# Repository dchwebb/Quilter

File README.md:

# Quilter

Quilter
--------

Quilter is a four-voice polyphonic analog low pass filter designed for use with the Eurorack Modular Synthesiser architecture.

As part of a range of compatilble Mountjoy Modular modules, polyphonic interconnections are made using RJ-45 cables (as used for Ethernet).

Each of the four filters is a four-pole self-oscillating low pass filter. Cutoff is controlled by a combination of shared signals (frequency potentiometer and jack socket) and two individual  controls frequency controls (one at approximately half the sensitivity of the other) available on RJ-45 connectors.

Resonance is controlled from a potentiometer with self-oscillation available at extreme settings.

Polyphonic output is available from an RJ-45 socket and a mixed output is available on a 3.5mm jack socket.

The module is built around the Sound Semiconductor SSI2144 Fatkeys Four-Pole Voltage Controlled Filter. A number of TL074/TL072 op-amps are used for control signal mixing, buffering and output amplification.

Two trimmer potentiometers are available for each voice to control volt per octave when using the filter in self-resonant mode, and frequency offset to control the base frequency of the cut-off of each voice.

Technical
---------

Construction is a sandwich of three PCBs with a component board, a controls board and a panel. PCBs designed in Kicad v6.

[Components schematic](https://raw.githubusercontent.com/dchwebb/Quilter/master/Quilter_Components.pdf)

[Controls schematic](https://raw.githubusercontent.com/dchwebb/Quilter/master/Quilter_Controls.pdf)

### Power

The Eurorack +/-12V rails have reverse polarity protection and filtering.

- +12V Current Draw: 52mA
- -12V Current Draw: 50mA

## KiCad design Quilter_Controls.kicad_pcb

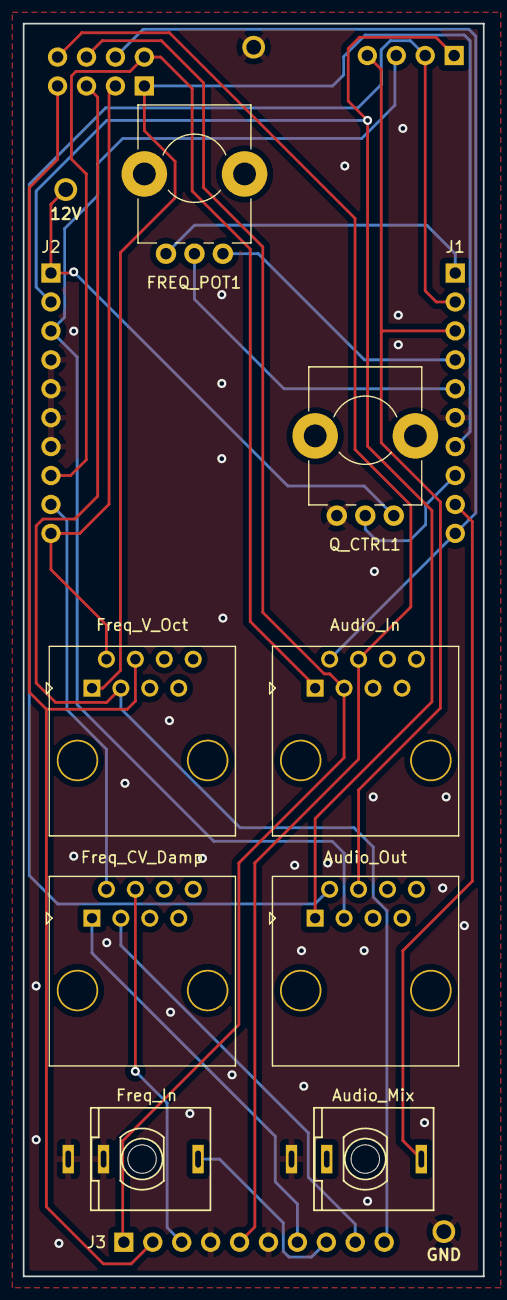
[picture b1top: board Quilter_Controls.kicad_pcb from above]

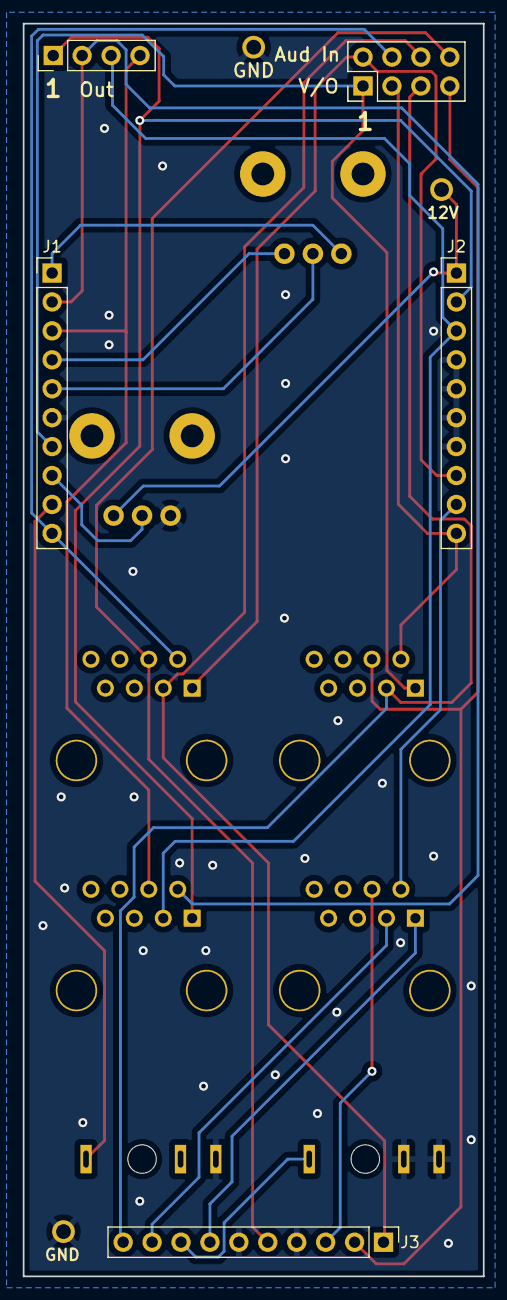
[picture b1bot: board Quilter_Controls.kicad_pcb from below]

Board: 2 copper layers, 40.4 x 110.0 mm, 16 parts (5 on the bottom side), 24 nets.

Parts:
FREQ_POT1: 10k; Alpha_9mm_Potentiometer_Aligned
J1, J2, J3: Conn_01x10_Male; PinHeader_1x10_P2.54mm_Vertical
J4: Audio_In; RJ45_Molex_42878-8506
J5: Audio_Out; RJ45_Molex_42878-8506
J6: Audio_Mix; THONKICONN_hole
J7: Freq_V_Oct; RJ45_Molex_42878-8506
J8: Freq_CV_Damp; RJ45_Molex_42878-8506
J9: Conn_02x04_Top_Bottom; PinHeader_2x04_P2.54mm_Vertical
J10: Conn_01x04_Male; PinHeader_1x04_P2.54mm_Vertical
J11: Freq_In; THONKICONN_hole
Q_CTRL1: 10k; Alpha_9mm_Potentiometer_Aligned
TP1, TP3, TP4: TestPoint; 1.3mm_Test_Point

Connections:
+12V: J2.1, Q_CTRL1.1, TP1.1
/AUDIO_BUFF1: J2.2, J5.1, J10.1
/AUDIO_BUFF2: J1.2, J5.2, J10.2
/AUDIO_BUFF3: J2.3, J5.3, J10.3
/AUDIO_BUFF4: J1.3, J5.4, J10.4
/AUDIO_IN1: J2.8, J4.1, J9.2
/AUDIO_IN2: J1.10, J4.2, J9.4
/AUDIO_IN3: J3.1, J4.3, J9.6
/AUDIO_IN4: J3.5, J4.4, J9.8
/AUDIO_MIX: J1.9, J6.3
/FREQ_CV_DAMP1: J3.7, J8.1
/FREQ_CV_DAMP2: J2.9, J8.2
/FREQ_CV_DAMP3: J3.9, J8.3
/FREQ_CV_DAMP4: J3.3, J8.4
/FREQ_JACK: J3.8, J11.3
/FREQ_POT: FREQ_POT1.2, J1.5
/FREQ_POT_5V: FREQ_POT1.1, J1.4
/FREQ_POT_-5V: FREQ_POT1.3, J1.1
/FREQ_V_OCT1: J1.7, J7.1, J9.1
/FREQ_V_OCT2: J2.10, J7.2, J9.3
/FREQ_V_OCT3: J3.10, J7.3, J9.5
/FREQ_V_OCT4: J3.2, J7.4, J9.7
/Q_POT: J1.8, Q_CTRL1.2
GND: J1.6, J2.4, J2.5, J2.6, J2.7, J3.4, J3.6, J6.1, J11.1, J11.2, Q_CTRL1.3, TP3.1, TP4.1

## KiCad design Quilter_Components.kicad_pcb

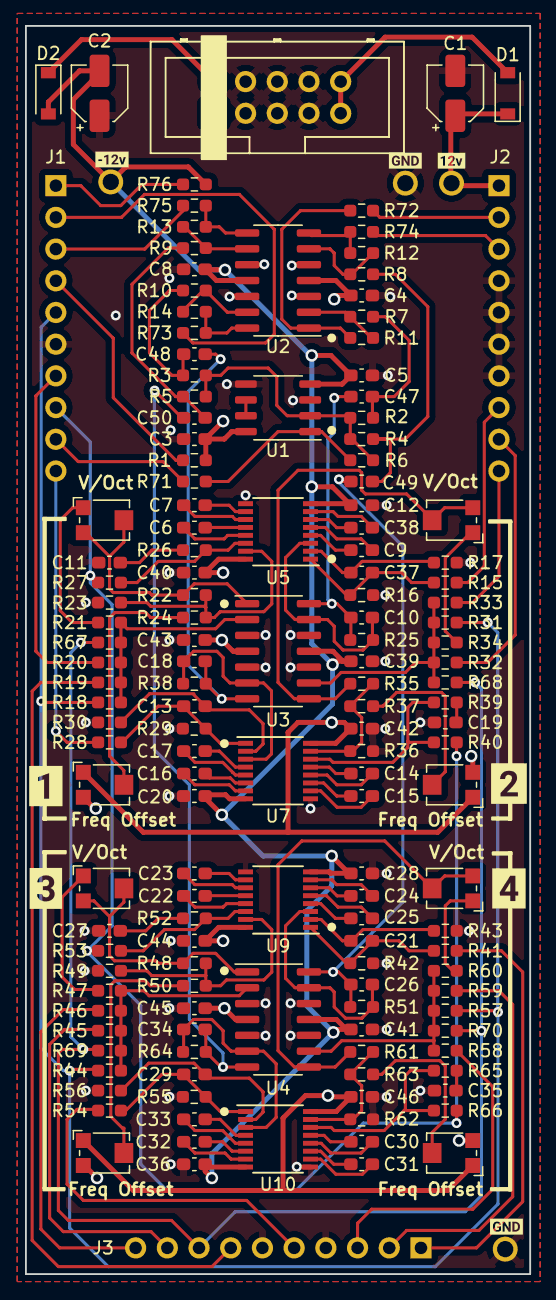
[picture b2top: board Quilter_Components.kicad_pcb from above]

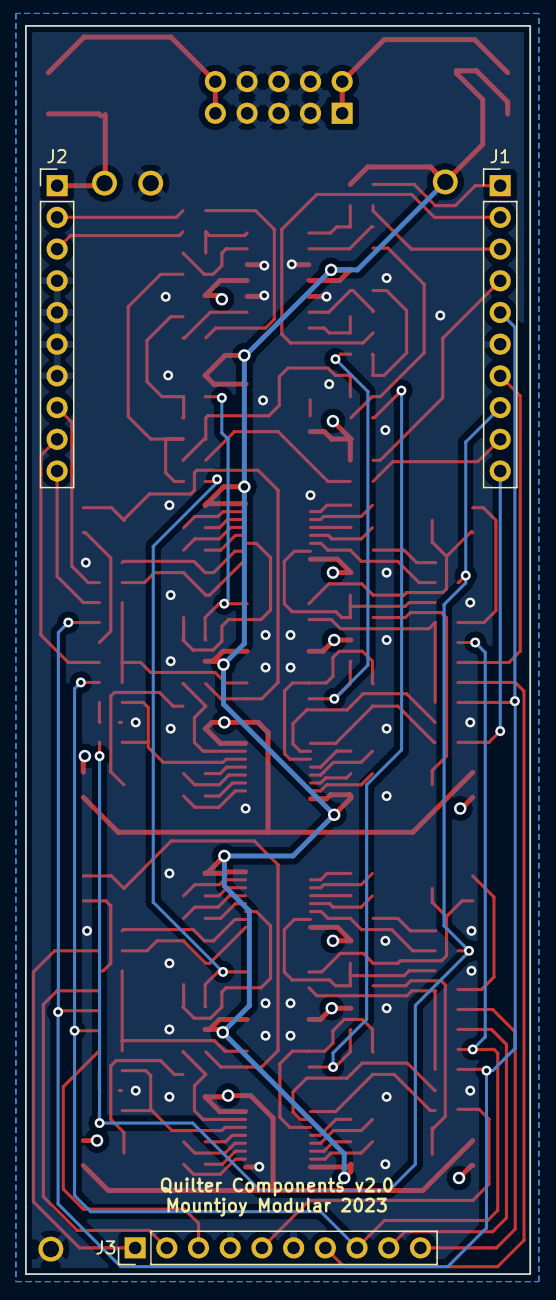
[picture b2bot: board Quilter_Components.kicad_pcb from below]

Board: 4 copper layers, 40.4 x 100.0 mm, 160 parts (3 on the bottom side), 118 nets.

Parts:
C1, C2: 22uF; CP_Elec_4x5.8
C3, C4, C5, C8, C12, C20, C28, C36, C39, C40, C41, C42, C43, C44, C45, C46: 1uF; C_0603_1608Metric_Pad1.08x0.95mm_HandSolder
C6, C7, C14, C15, C16, C22, C23, C24, C30, C31, C32, C38: 6.8nF_C0G; C_0603_1608Metric_Pad1.08x0.95mm_HandSolder
C9, C17, C25, C33: 560pF_C0G; C_0603_1608Metric_Pad1.08x0.95mm_HandSolder
C10, C18, C26, C34: 100pF; C_0603_1608Metric_Pad1.08x0.95mm_HandSolder
C11, C19, C27, C35: 10nF; C_0603_1608Metric_Pad1.08x0.95mm_HandSolder
C13, C21, C29, C37: 3.3nF; C_0603_1608Metric_Pad1.08x0.95mm_HandSolder
C47, C48, C49, C50: 10uF; C_0603_1608Metric_Pad1.08x0.95mm_HandSolder
D1, D2: 1N5819; D_SOD-123
FREQ_OFFSET1, FREQ_OFFSET2, FREQ_OFFSET3, FREQ_OFFSET4: 50k; Potentiometer_Bourns_TC33X_Vertical
J1, J2, J3: Conn_01x10_Male; PinHeader_1x10_P2.54mm_Vertical
J4: Eurorack_10_pin_power; Eurorack_10_pin_header
R1, R76: 14k; R_0603_1608Metric_Pad0.98x0.95mm_HandSolder
R2, R3, R4, R5, R7, R8, R9, R10, R11, R12, R13, R14: 10k; R_0603_1608Metric_Pad0.98x0.95mm_HandSolder
R6: 4.7k; R_0603_1608Metric_Pad0.98x0.95mm_HandSolder
R15, R28, R41, R54: 68k; R_0603_1608Metric_Pad0.98x0.95mm_HandSolder
R16, R17, R29, R30, R42, R43, R55, R56: 200; R_0603_1608Metric_Pad0.98x0.95mm_HandSolder
R18, R20, R22, R31, R33, R35, R44, R46, R48, R57, R59, R61, R67, R68, R69, R70: 100k; R_0603_1608Metric_Pad0.98x0.95mm_HandSolder
R19, R32, R45, R58: 220k; R_0603_1608Metric_Pad0.98x0.95mm_HandSolder
R21, R34, R47, R60: 160k; R_0603_1608Metric_Pad0.98x0.95mm_HandSolder
R23, R36, R49, R62, R71, R72, R73, R74, R75: 1k; R_0603_1608Metric_Pad0.98x0.95mm_HandSolder
R24, R37, R50, R63: 499k; R_0603_1608Metric_Pad0.98x0.95mm_HandSolder
R25, R38, R51, R64: 33k; R_0603_1608Metric_Pad0.98x0.95mm_HandSolder
R26, R39, R52, R65: 499; R_0603_1608Metric_Pad0.98x0.95mm_HandSolder
R27, R40, R53, R66: 24k; R_0603_1608Metric_Pad0.98x0.95mm_HandSolder
TP1, TP2, TP3, TP4: TestPoint; 1.3mm_Test_Point
U1: TL072; SO-8_3.9x4.9mm_P1.27mm
U2, U3, U4: TL074; SOIC-14_3.9x8.7mm_P1.27mm
U5, U7, U9, U10: SSI2144; SSOP-16_3.9x4.9mm_P0.635mm
V_OCT1, V_OCT2, V_OCT3, V_OCT4: 50k; Potentiometer_Bourns_TC33X_Vertical
kibuzzard-63F9EC4B: G***; kibuzzard-63F9EC4B
kibuzzard-63F9ECEE: G***; kibuzzard-63F9ECEE
kibuzzard-63FCE890: G***; kibuzzard-63FCE890
kibuzzard-63FCEF0D: G***; kibuzzard-63FCEF0D
kibuzzard-640237A8: G***; kibuzzard-640237A8
kibuzzard-640237DF, kibuzzard-640237DF#2: G***; kibuzzard-640237DF
kibuzzard-640237FD: G***; kibuzzard-640237FD

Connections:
+12V: C1.1, C3.1, C4.1, C40.1, C42.1, C43.1, C44.1, C45.1, C46.1, D1.1 (K), FREQ_OFFSET1.1, FREQ_OFFSET2.1, FREQ_OFFSET3.1, FREQ_OFFSET4.1, J2.1, R1.1, TP1.1, U1.8 (V+), U2.4 (V+), U3.4 (V+), U4.4 (V+), U5.16 (V+), U7.16 (V+), U9.16 (V+), U10.16 (V+)
-12V: C2.2, C5.1, C8.1, C12.2, C20.2, C28.2, C36.2, C39.1, C41.1, D2.2 (A), FREQ_OFFSET1.3, FREQ_OFFSET2.3, FREQ_OFFSET3.3, FREQ_OFFSET4.3, R76.1, TP2.1, U1.4 (V-), U2.11 (V-), U3.11 (V-), U4.11 (V-), U5.8 (V-), U7.8 (V-), U9.8 (V-), U10.8 (V-)
/+12V_IN: D1.2 (A), J4.9, J4.10
/-12V_IN: D2.1 (K), J4.1, J4.2
/AUDIO_BUFF1: J2.2, R72.2
/AUDIO_BUFF2: J1.2, R73.2
/AUDIO_BUFF3: J2.3, R74.2
/AUDIO_BUFF4: J1.3, R75.2
/AUDIO_IN1: J2.8, R15.2
/AUDIO_IN2: J1.10, R28.2
/AUDIO_IN3: J3.1, R41.2
/AUDIO_IN4: J3.5, R54.2
/AUDIO_MIX: J1.9, R71.2
/Audio_Out1: C47.1, R2.2, R7.2
/Audio_Out2: C48.1, R3.2, R10.2
/Audio_Out3: C49.1, R4.2, R8.2
/Audio_Out4: C50.1, R5.2, R9.2
/FREQ_CV_DAMP1: J3.7, R19.2
/FREQ_CV_DAMP2: J2.9, R32.2
/FREQ_CV_DAMP3: J3.9, R45.2
/FREQ_CV_DAMP4: J3.3, R58.2
/FREQ_JACK: J3.8, R67.2, R68.2, R69.2, R70.2
/FREQ_POT: J1.5, R18.2, R31.2, R44.2, R57.2
/FREQ_POT_5V: J1.4, R1.2
/FREQ_POT_-5V: J1.1, R76.2
/FREQ_V_OCT1: J1.7, R20.2
/FREQ_V_OCT2: J2.10, R33.2
/FREQ_V_OCT3: J3.10, R46.2
/FREQ_V_OCT4: J3.2, R59.2
/Filter_Voice1/FREQ_CTRL: R22.1, R23.1, R24.1, U5.15 (FREQ_CTRL)
/Filter_Voice1/Q_CTRL: R26.2, R27.2, U5.14 (Q_CTRL)
/Filter_Voice2/FREQ_CTRL: R35.1, R36.1, R37.1, U7.15 (FREQ_CTRL)
/Filter_Voice2/Q_CTRL: R39.2, R40.2, U7.14 (Q_CTRL)
/Filter_Voice3/FREQ_CTRL: R48.1, R49.1, R50.1, U9.15 (FREQ_CTRL)
/Filter_Voice3/Q_CTRL: R52.2, R53.2, U9.14 (Q_CTRL)
/Filter_Voice4/FREQ_CTRL: R61.1, R62.1, R63.1, U10.15 (FREQ_CTRL)
/Filter_Voice4/Q_CTRL: R65.2, R66.2, U10.14 (Q_CTRL)
/Q_POT: J1.8, R27.1, R40.1, R53.1, R66.1
GND: C1.2, C2.1, C3.2, C4.2, C5.2, C8.2, C11.2, C12.1, C19.2, C20.1, C27.2, C28.1, C35.2, C36.1, C39.2, C40.2, C41.2, C42.2, C43.2, C44.2, C45.2, C46.2, J1.6, J2.4, J2.5, J2.6, J2.7, J3.4, J3.6, J4.3, J4.4, J4.5, J4.6, J4.7, J4.8, R16.1, R17.2, R23.2, R29.1, R30.2, R36.2, R42.1, R43.2, R49.2, R55.1, R56.2, R62.2, TP3.1, TP4.1, U1.3 (+), U1.5 (+), U2.3 (+), U2.5 (+), U2.10 (+), U2.12 (+), U3.3 (+), U3.5 (+), U3.10 (+), U3.12 (+), U4.3 (+), U4.5 (+), U4.10 (+), U4.12 (+), U5.9 (GND), U7.9 (GND), U9.9 (GND), U10.9 (GND)
unnamed: C6.1, U5.13 (C1A)
unnamed: C6.2, U5.12 (C1B)
unnamed: C7.1, U5.11 (C2A)
unnamed: C7.2, U5.10 (C2B)
unnamed: C9.1, U5.4 (C4A)
unnamed: C9.2, U5.5 (C4B)
unnamed: C10.1, C47.2, R25.1, U3.14
unnamed: C10.2, R25.2, U3.13 (-), U5.3 (OUT)
unnamed: C11.1, R26.1
unnamed: C13.1, R30.1, U7.2 (SIG_IN-)
unnamed: C13.2, R28.1, R29.2, U7.1 (SIG_IN+)
unnamed: C14.1, U7.13 (C1A)
unnamed: C14.2, U7.12 (C1B)
unnamed: C15.1, U7.11 (C2A)
unnamed: C15.2, U7.10 (C2B)
unnamed: C16.1, U7.6 (C3A)
unnamed: C16.2, U7.7 (C3B)
unnamed: C17.1, U7.4 (C4A)
unnamed: C17.2, U7.5 (C4B)
unnamed: C18.1, C48.2, R38.1, U3.7
unnamed: C18.2, R38.2, U3.6 (-), U7.3 (OUT)
unnamed: C19.1, R39.1
unnamed: C21.1, R43.1, U9.2 (SIG_IN-)
unnamed: C21.2, R41.1, R42.2, U9.1 (SIG_IN+)
unnamed: C22.1, U9.13 (C1A)
unnamed: C22.2, U9.12 (C1B)
unnamed: C23.1, U9.11 (C2A)
unnamed: C23.2, U9.10 (C2B)
unnamed: C24.1, U9.6 (C3A)
unnamed: C24.2, U9.7 (C3B)
unnamed: C25.1, U9.4 (C4A)
unnamed: C25.2, U9.5 (C4B)
unnamed: C26.1, C49.2, R51.1, U4.14
unnamed: C26.2, R51.2, U4.13 (-), U9.3 (OUT)
unnamed: C27.1, R52.1
unnamed: C29.1, R56.1, U10.2 (SIG_IN-)
unnamed: C29.2, R54.1, R55.2, U10.1 (SIG_IN+)
unnamed: C30.1, U10.13 (C1A)
unnamed: C30.2, U10.12 (C1B)
unnamed: C31.1, U10.11 (C2A)
unnamed: C31.2, U10.10 (C2B)
unnamed: C32.1, U10.6 (C3A)
unnamed: C32.2, U10.7 (C3B)
unnamed: C33.1, U10.4 (C4A)
unnamed: C33.2, U10.5 (C4B)
unnamed: C34.1, C50.2, R64.1, U4.7
unnamed: C34.2, R64.2, U4.6 (-), U10.3 (OUT)
unnamed: C35.1, R65.1
unnamed: C37.1, R17.1, U5.2 (SIG_IN-)
unnamed: C37.2, R15.1, R16.2, U5.1 (SIG_IN+)
unnamed: C38.1, U5.6 (C3A)
unnamed: C38.2, U5.7 (C3B)
unnamed: FREQ_OFFSET1.2, R24.2
unnamed: FREQ_OFFSET2.2, R37.2
unnamed: FREQ_OFFSET3.2, R50.2
unnamed: FREQ_OFFSET4.2, R63.2
unnamed: R2.1, R3.1, R4.1, R5.1, R6.2, U1.2 (-)
unnamed: R6.1, R71.1, U1.1
unnamed: R10.1, R14.2, U2.13 (-)
unnamed: R11.1, R72.1, U2.1
unnamed: R7.1, R11.2, U2.2 (-)
unnamed: R12.1, R74.1, U2.7
unnamed: R8.1, R12.2, U2.6 (-)
unnamed: R13.1, R75.1, U2.8
unnamed: R9.1, R13.2, U2.9 (-)
unnamed: R14.1, R73.1, U2.14
unnamed: R18.1, R19.1, R20.1, R21.2, R67.1, U3.2 (-)
unnamed: R21.1, V_OCT1.1
unnamed: R22.2, U3.1, V_OCT1.2, V_OCT1.3
unnamed: R31.1, R32.1, R33.1, R34.2, R68.1, U3.9 (-)
unnamed: R34.1, V_OCT2.1
unnamed: R35.2, U3.8, V_OCT2.2, V_OCT2.3
unnamed: R44.1, R45.1, R46.1, R47.2, R69.1, U4.2 (-)
unnamed: R47.1, V_OCT3.1
unnamed: R48.2, U4.1, V_OCT3.2, V_OCT3.3
unnamed: R57.1, R58.1, R59.1, R60.2, R70.1, U4.9 (-)
unnamed: R60.1, V_OCT4.1
unnamed: R61.2, U4.8, V_OCT4.2, V_OCT4.3
unnamed: U1.6 (-), U1.7

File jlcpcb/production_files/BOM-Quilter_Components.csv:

Comment,Designator,Footprint,LCSC
100pF,"C10,C18,C26,C34",C_0603_1608Metric_Pad1.08x0.95mm_HandSolder,C14858
1uF,"C12,C20,C28,C3,C36,C39,C4,C40,C41,C42,C43,C44,C45,C46,C5,C8",C_0603_1608Metric_Pad1.08x0.95mm_HandSolder,C15849
3.3nF,"C13,C21,C29,C37",C_0603_1608Metric_Pad1.08x0.95mm_HandSolder,C1613
6.8nF_C0G,"C14,C15,C16,C22,C23,C24,C30,C31,C32,C38,C6,C7",C_0603_1608Metric_Pad1.08x0.95mm_HandSolder,C162241
10uF,"C47,C48,C49,C50",C_0603_1608Metric_Pad1.08x0.95mm_HandSolder,C19702
1k,"R23,R36,R49,R62,R71,R72,R73,R74,R75",R_0603_1608Metric_Pad0.98x0.95mm_HandSolder,C21190
160k,"R21,R34,R47,R60",R_0603_1608Metric_Pad0.98x0.95mm_HandSolder,C22813
220k,"R19,R32,R45,R58",R_0603_1608Metric_Pad0.98x0.95mm_HandSolder,C22961
4.7k,R6,R_0603_1608Metric_Pad0.98x0.95mm_HandSolder,C23162
68k,"R15,R28,R41,R54",R_0603_1608Metric_Pad0.98x0.95mm_HandSolder,C23231
24k,"R27,R40,R53,R66",R_0603_1608Metric_Pad0.98x0.95mm_HandSolder,C23352
100k,"R18,R20,R22,R31,R33,R35,R44,R46,R48,R57,R59,R61,R67,R68,R69,R70",R_0603_1608Metric_Pad0.98x0.95mm_HandSolder,C25803
10k,"R10,R11,R12,R13,R14,R2,R3,R4,R5,R7,R8,R9",R_0603_1608Metric_Pad0.98x0.95mm_HandSolder,C25804
33k,"R25,R38,R51,R64",R_0603_1608Metric_Pad0.98x0.95mm_HandSolder,C4216
10nF,"C11,C19,C27,C35",C_0603_1608Metric_Pad1.08x0.95mm_HandSolder,C57112
TL072,U1,SO-8_3.9x4.9mm_P1.27mm,C6961
200,"R16,R17,R29,R30,R42,R43,R55,R56",R_0603_1608Metric_Pad0.98x0.95mm_HandSolder,C8218
1N5819,"D1,D2",D_SOD-123,C8598

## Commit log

2023-02-22 Started component PCB layout
2023-02-22 First draft of component PCB routed
2023-02-22 Started Controls PCB
2023-02-23 Started layout for 8HP alternative
2023-02-23 Draft of 8HP component PCB routed
2023-02-23 First draft routing of Controls PCB
2023-02-24 Fixed orientation of connector headers
2023-02-24 Started Panel Layout
2023-02-24 Reorganisation of component board
2023-02-24 Re-routed Controls board
2023-02-26 Added all voice filter CV; panel draft done
2023-02-26 Updates to panel and component boards
2023-02-27 Finished routing components and controls
2023-02-27 Schematic formatting
2023-03-02 Cleaned up panel and PCBs
2023-03-02 Updated panel and BOM
2023-03-03 Added op-amp output protection resistors
2023-03-04 Generated Gerbers for Production
2023-03-22 Added Readme and revision notes
2023-06-26 Started adding DC blocking caps to audio outputs
2023-07-04 Updates for v2, including dc blocking caps on output
    Also adjusted lower range of cutoff knob and tweaked various resistor values
2023-07-05 Reorganised components gerber location
2023-07-06 Prepared v2 Controls and Components for manufacture
2023-07-19 Updated to Kicad 7
